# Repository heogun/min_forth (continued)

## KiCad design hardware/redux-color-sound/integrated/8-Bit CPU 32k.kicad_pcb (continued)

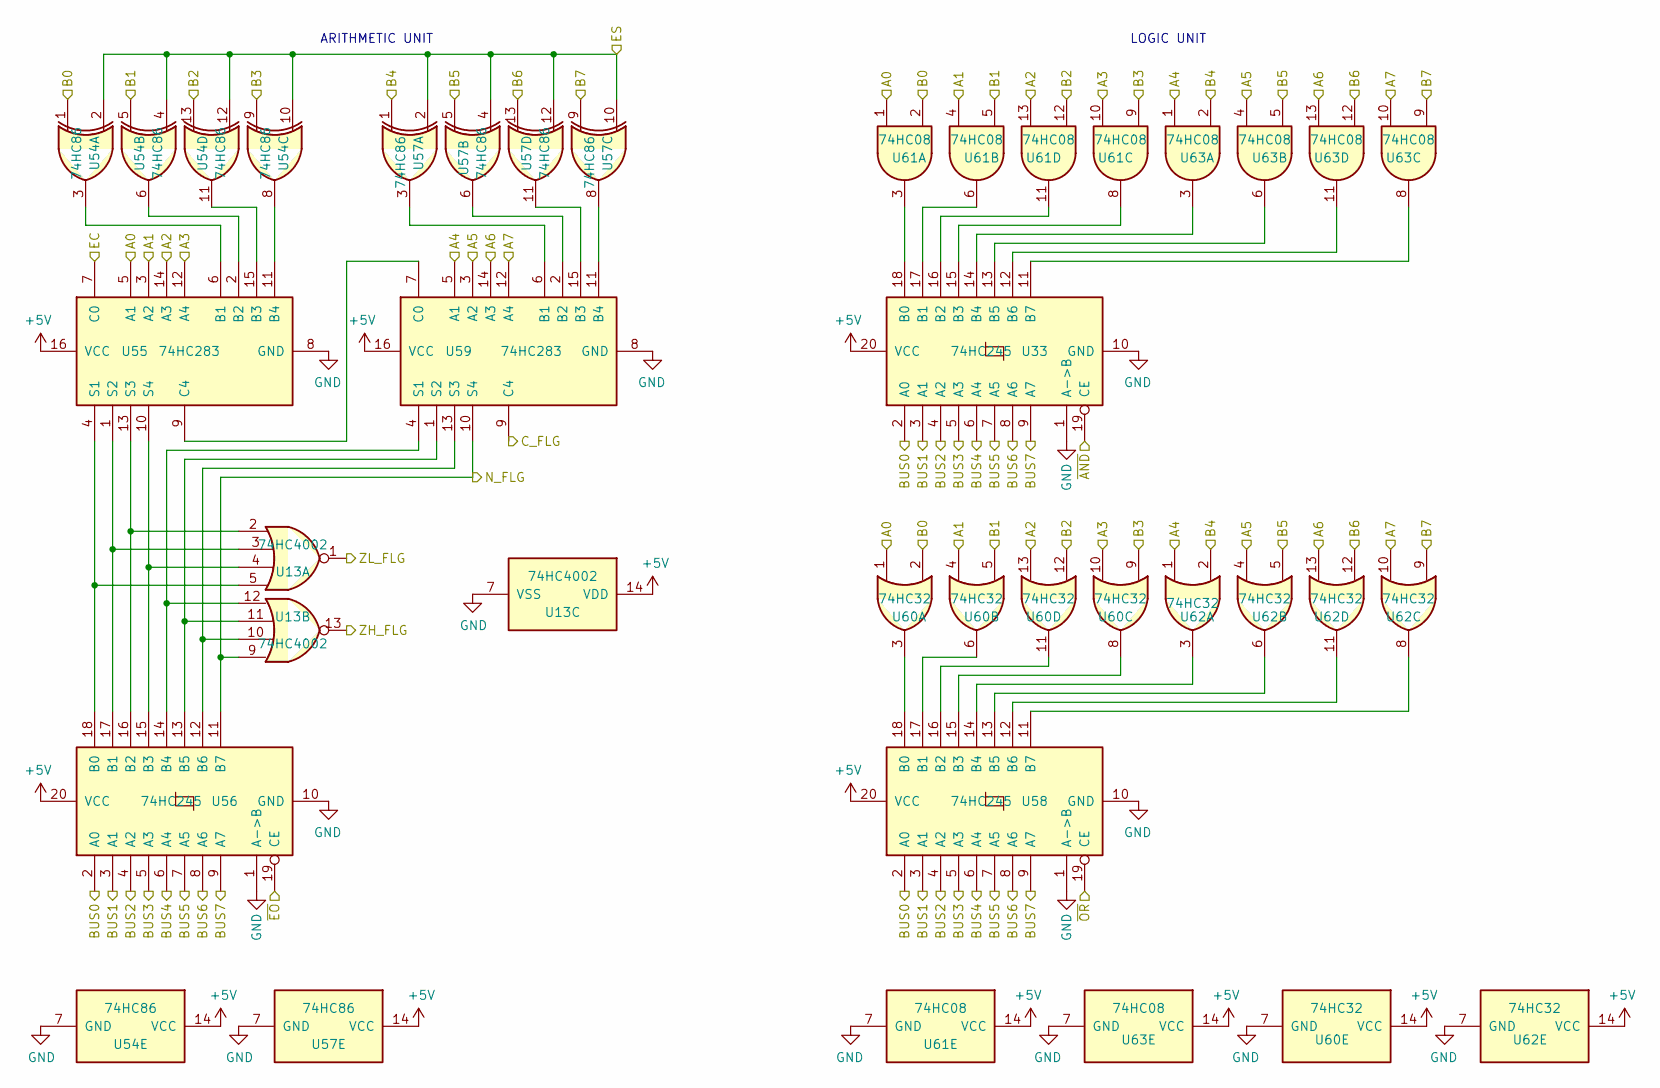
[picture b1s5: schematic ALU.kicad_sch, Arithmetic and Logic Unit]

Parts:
U13: 74HC4002; DIP-14_W7.62mm_Socket
U33, U56, U58: 74HC245; DIP-20_W7.62mm_Socket
U54, U57: 74HC86; DIP-14_W7.62mm_Socket
U55, U59: 74HC283; DIP-16_W7.62mm_Socket
U60, U62: 74HC32; DIP-14_W7.62mm_Socket
U61, U63: 74HC08; DIP-14_W7.62mm_Socket

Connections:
+5V: U13.14 (VDD), U33.20 (VCC), U54.14 (VCC), U55.16 (VCC), U56.20 (VCC), U57.14 (VCC), U58.20 (VCC), U59.16 (VCC), U60.14 (VCC), U61.14 (VCC), U62.14 (VCC), U63.14 (VCC); also elsewhere on the board
/ALU/A0: U55.5 (A1), U60.1, U61.1; also elsewhere on the board
/ALU/A1: U55.3 (A2), U60.4, U61.4; also elsewhere on the board
/ALU/A2: U55.14 (A3), U60.13, U61.13; also elsewhere on the board
/ALU/A3: U55.12 (A4), U60.10, U61.10; also elsewhere on the board
/ALU/A4: U59.5 (A1), U62.1, U63.1; also elsewhere on the board
/ALU/A5: U59.3 (A2), U62.4, U63.4; also elsewhere on the board
/ALU/A6: U59.14 (A3), U62.13, U63.13; also elsewhere on the board
/ALU/A7: U59.12 (A4), U62.10, U63.10; also elsewhere on the board
/ALU/B0: U54.1, U60.2, U61.2; also elsewhere on the board
/ALU/B1: U54.5, U60.5, U61.5; also elsewhere on the board
/ALU/B2: U54.13, U60.12, U61.12; also elsewhere on the board
/ALU/B3: U54.9, U60.9, U61.9; also elsewhere on the board
/ALU/B4: U57.1, U62.2, U63.2; also elsewhere on the board
/ALU/B5: U57.5, U62.5, U63.5; also elsewhere on the board
/ALU/B6: U57.13, U62.12, U63.12; also elsewhere on the board
/ALU/B7: U57.9, U62.9, U63.9; also elsewhere on the board
/ALU/C_FLG: U59.9 (C4); also elsewhere on the board
/ALU/EC: U55.7 (C0); also elsewhere on the board
/ALU/ES: U54.2, U54.4, U54.10, U54.12, U57.2, U57.4, U57.10, U57.12; also elsewhere on the board
/ALU/N_FLG: U13.9, U56.11 (B7), U59.10 (S4); also elsewhere on the board
/ALU/ZH_FLG: U13.13; also elsewhere on the board
/ALU/ZL_FLG: U13.1; also elsewhere on the board
/ALU/~AND: U33.19 (CE); also elsewhere on the board
/ALU/~EO: U56.19 (CE); also elsewhere on the board
/ALU/~OR: U58.19 (CE); also elsewhere on the board
BUS0: U33.2 (A0), U56.2 (A0), U58.2 (A0); also elsewhere on the board
BUS1: U33.3 (A1), U56.3 (A1), U58.3 (A1); also elsewhere on the board
BUS2: U33.4 (A2), U56.4 (A2), U58.4 (A2); also elsewhere on the board
BUS3: U33.5 (A3), U56.5 (A3), U58.5 (A3); also elsewhere on the board
BUS4: U33.6 (A4), U56.6 (A4), U58.6 (A4); also elsewhere on the board
BUS5: U33.7 (A5), U56.7 (A5), U58.7 (A5); also elsewhere on the board
BUS6: U33.8 (A6), U56.8 (A6), U58.8 (A6); also elsewhere on the board
BUS7: U33.9 (A7), U56.9 (A7), U58.9 (A7); also elsewhere on the board
GND: U13.7 (VSS), U33.1 (A->B), U33.10 (GND), U54.7 (GND), U55.8 (GND), U56.1 (A->B), U56.10 (GND), U57.7 (GND), U58.1 (A->B), U58.10 (GND), U59.8 (GND), U60.7 (GND), U61.7 (GND), U62.7 (GND), U63.7 (GND); also elsewhere on the board
unnamed: U33.18 (B0), U61.3
unnamed: U33.17 (B1), U61.6
unnamed: U33.16 (B2), U61.11
unnamed: U33.15 (B3), U61.8
unnamed: U33.14 (B4), U63.3
unnamed: U33.13 (B5), U63.6
unnamed: U33.12 (B6), U63.11
unnamed: U33.11 (B7), U63.8
unnamed: U54.3, U55.6 (B1)
unnamed: U54.6, U55.2 (B2)
unnamed: U54.11, U55.15 (B3)
unnamed: U54.8, U55.11 (B4)
unnamed: U55.9 (C4), U59.7 (C0)
unnamed: U13.5, U55.4 (S1), U56.18 (B0)
unnamed: U13.3, U55.1 (S2), U56.17 (B1)
unnamed: U13.2, U55.13 (S3), U56.16 (B2)
unnamed: U13.4, U55.10 (S4), U56.15 (B3)
unnamed: U13.12, U56.14 (B4), U59.4 (S1)
unnamed: U13.11, U56.13 (B5), U59.1 (S2)
unnamed: U13.10, U56.12 (B6), U59.13 (S3)
unnamed: U58.18 (B0), U60.3
unnamed: U58.17 (B1), U60.6
unnamed: U58.16 (B2), U60.11
unnamed: U58.15 (B3), U60.8
unnamed: U58.14 (B4), U62.3
unnamed: U58.13 (B5), U62.6
unnamed: U58.12 (B6), U62.11
unnamed: U58.11 (B7), U62.8
unnamed: U57.3, U59.6 (B1)
unnamed: U57.6, U59.2 (B2)
unnamed: U57.11, U59.15 (B3)
unnamed: U57.8, U59.11 (B4)

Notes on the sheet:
ARITHMETIC UNIT
LOGIC UNIT

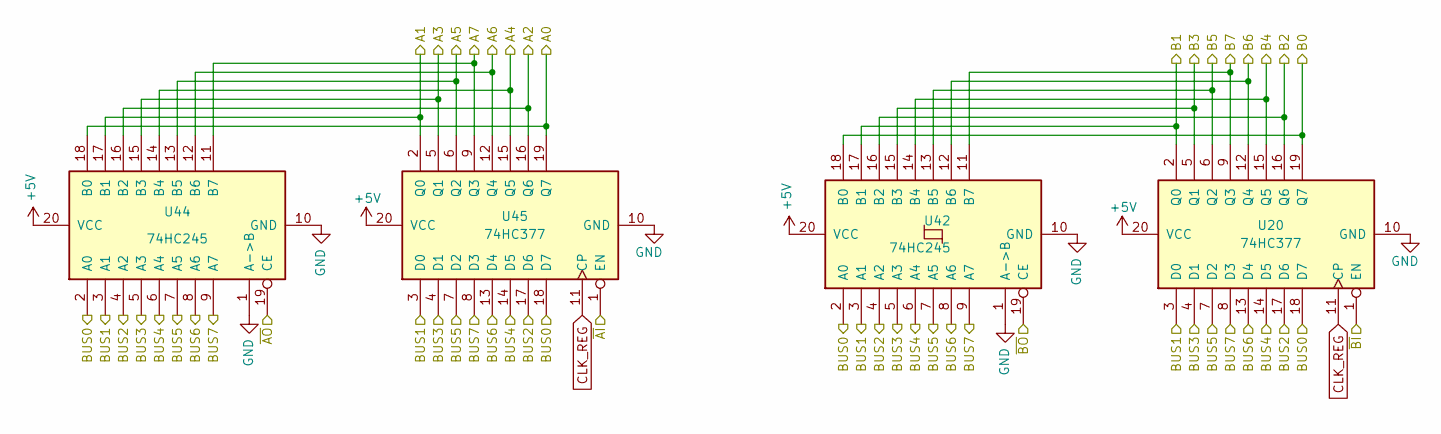
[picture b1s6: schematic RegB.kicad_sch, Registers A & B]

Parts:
U20, U45: 74HC377; DIP-20_W7.62mm_Socket
U42, U44: 74HC245; DIP-20_W7.62mm_Socket

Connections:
+5V: U20.20 (VCC), U42.20 (VCC), U44.20 (VCC), U45.20 (VCC); also elsewhere on the board
/ALU/A0: U44.18 (B0), U45.19 (Q7); also elsewhere on the board
/ALU/A1: U44.17 (B1), U45.2 (Q0); also elsewhere on the board
/ALU/A2: U44.16 (B2), U45.16 (Q6); also elsewhere on the board
/ALU/A3: U44.15 (B3), U45.5 (Q1); also elsewhere on the board
/ALU/A4: U44.14 (B4), U45.15 (Q5); also elsewhere on the board
/ALU/A5: U44.13 (B5), U45.6 (Q2); also elsewhere on the board
/ALU/A6: U44.12 (B6), U45.12 (Q4); also elsewhere on the board
/ALU/A7: U44.11 (B7), U45.9 (Q3); also elsewhere on the board
/ALU/B0: U20.19 (Q7), U42.18 (B0); also elsewhere on the board
/ALU/B1: U20.2 (Q0), U42.17 (B1); also elsewhere on the board
/ALU/B2: U20.16 (Q6), U42.16 (B2); also elsewhere on the board
/ALU/B3: U20.5 (Q1), U42.15 (B3); also elsewhere on the board
/ALU/B4: U20.15 (Q5), U42.14 (B4); also elsewhere on the board
/ALU/B5: U20.6 (Q2), U42.13 (B5); also elsewhere on the board
/ALU/B6: U20.12 (Q4), U42.12 (B6); also elsewhere on the board
/ALU/B7: U20.9 (Q3), U42.11 (B7); also elsewhere on the board
/Control Logic/~AI: U45.1 (EN); also elsewhere on the board
/Control Logic/~AO: U44.19 (CE); also elsewhere on the board
/Control Logic/~BI: U20.1 (EN); also elsewhere on the board
/Control Logic/~BO: U42.19 (CE); also elsewhere on the board
BUS0: U20.18 (D7), U42.2 (A0), U44.2 (A0), U45.18 (D7); also elsewhere on the board
BUS1: U20.3 (D0), U42.3 (A1), U44.3 (A1), U45.3 (D0); also elsewhere on the board
BUS2: U20.17 (D6), U42.4 (A2), U44.4 (A2), U45.17 (D6); also elsewhere on the board
BUS3: U20.4 (D1), U42.5 (A3), U44.5 (A3), U45.4 (D1); also elsewhere on the board
BUS4: U20.14 (D5), U42.6 (A4), U44.6 (A4), U45.14 (D5); also elsewhere on the board
BUS5: U20.7 (D2), U42.7 (A5), U44.7 (A5), U45.7 (D2); also elsewhere on the board
BUS6: U20.13 (D4), U42.8 (A6), U44.8 (A6), U45.13 (D4); also elsewhere on the board
BUS7: U20.8 (D3), U42.9 (A7), U44.9 (A7), U45.8 (D3); also elsewhere on the board
CLK_REG: U20.11 (CP), U45.11 (CP); also elsewhere on the board
GND: U20.10 (GND), U42.1 (A->B), U42.10 (GND), U44.1 (A->B), U44.10 (GND), U45.10 (GND); also elsewhere on the board

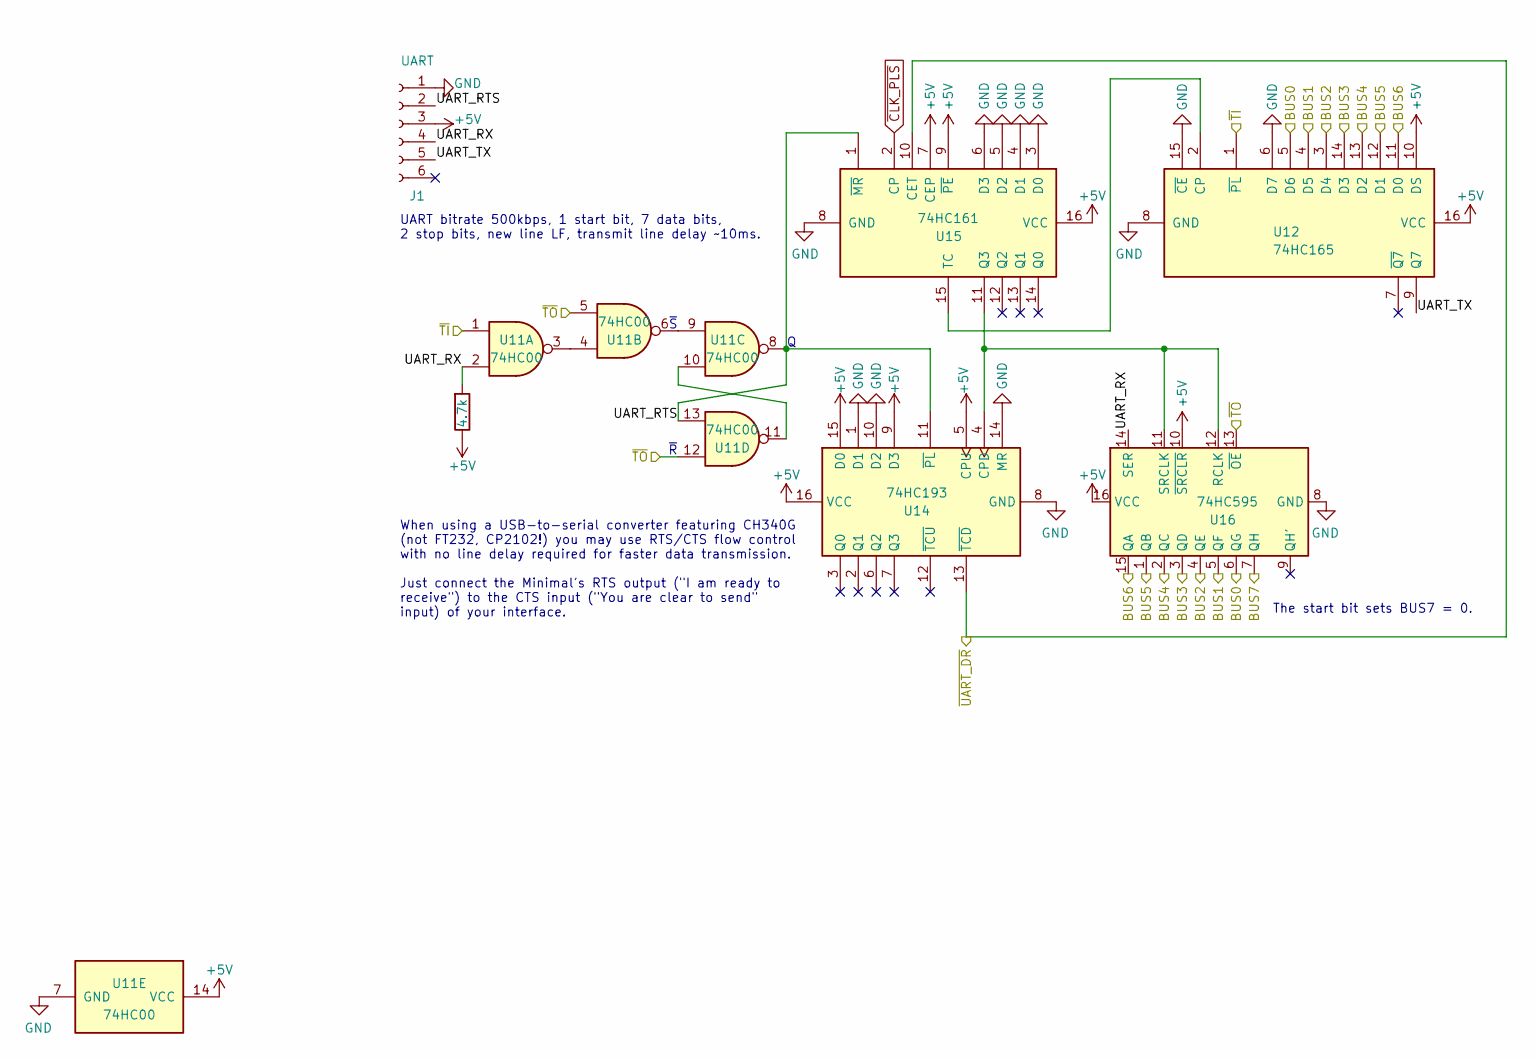
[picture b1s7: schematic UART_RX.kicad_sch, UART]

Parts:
J1: UART; PinSocket_1x06_P2.54mm_Vertical
R1: 4.7k; R_Axial_DIN0207_L6.3mm_D2.5mm_P7.62mm_Horizontal
U11: 74HC00; DIP-14_W7.62mm_Socket
U12: 74HC165; DIP-16_W7.62mm_Socket
U14: 74HC193; DIP-16_W7.62mm_Socket
U15: 74HC161; DIP-16_W7.62mm_Socket
U16: 74HC595; DIP-16_W7.62mm_Socket

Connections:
+5V: J1.3, R1.1, U11.14 (VCC), U12.10 (DS), U12.16 (VCC), U14.5 (CPU), U14.9 (D3), U14.15 (D0), U14.16 (VCC), U15.7 (CEP), U15.9 (~PE), U15.16 (VCC), U16.10 (~SRCLR), U16.16 (VCC); also elsewhere on the board
/Control Logic/~TI: U11.1, U12.1 (~PL); also elsewhere on the board
/Control Logic/~TO: U11.5, U11.12, U16.13 (~OE); also elsewhere on the board
/Control Logic/~UART_DR: U14.13 (~TCD), U15.10 (CET); also elsewhere on the board
/UART/UART_RTS: J1.2, U11.8, U11.13, U14.11 (~PL), U15.1 (~MR)
/UART/UART_RX: J1.4, R1.2, U11.2, U16.14 (SER)
/UART/UART_TX: J1.5, U12.9 (Q7)
BUS0: U12.5 (D6), U16.6 (QG); also elsewhere on the board
BUS1: U12.4 (D5), U16.5 (QF); also elsewhere on the board
BUS2: U12.3 (D4), U16.4 (QE); also elsewhere on the board
BUS3: U12.14 (D3), U16.3 (QD); also elsewhere on the board
BUS4: U12.13 (D2), U16.2 (QC); also elsewhere on the board
BUS5: U12.12 (D1), U16.1 (QB); also elsewhere on the board
BUS6: U12.11 (D0), U16.15 (QA); also elsewhere on the board
BUS7: U16.7 (QH); also elsewhere on the board
GND: J1.1, U11.7 (GND), U12.6 (D7), U12.8 (GND), U12.15 (~CE), U14.1 (D1), U14.8 (GND), U14.10 (D2), U14.14 (MR), U15.3 (D0), U15.4 (D1), U15.5 (D2), U15.6 (D3), U15.8 (GND), U16.8 (GND); also elsewhere on the board
unnamed: U11.3, U11.4
unnamed: U11.6, U11.9
unnamed: U11.10, U11.11
unnamed: U12.2 (CP), U15.15 (TC)
unnamed: U14.4 (CPD), U15.11 (Q3), U16.11 (SRCLK), U16.12 (RCLK)
~CLK_PLS: U15.2 (CP); also elsewhere on the board

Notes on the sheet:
~{S}
UART bitrate 500kbps, 1 start bit, 7 data bits, 2 stop bits, new line LF, transmit line delay ~10ms.
~{R}
The start bit sets BUS7 = 0.
When using a USB-to-serial converter featuring CH340G (not FT232, CP2102!) you may use RTS/CTS flow control with no line delay required for faster data transmission. Just connect the Minimal's RTS output ("I am ready to receive") to the CTS input ("You are clear to send" input) of your interface.

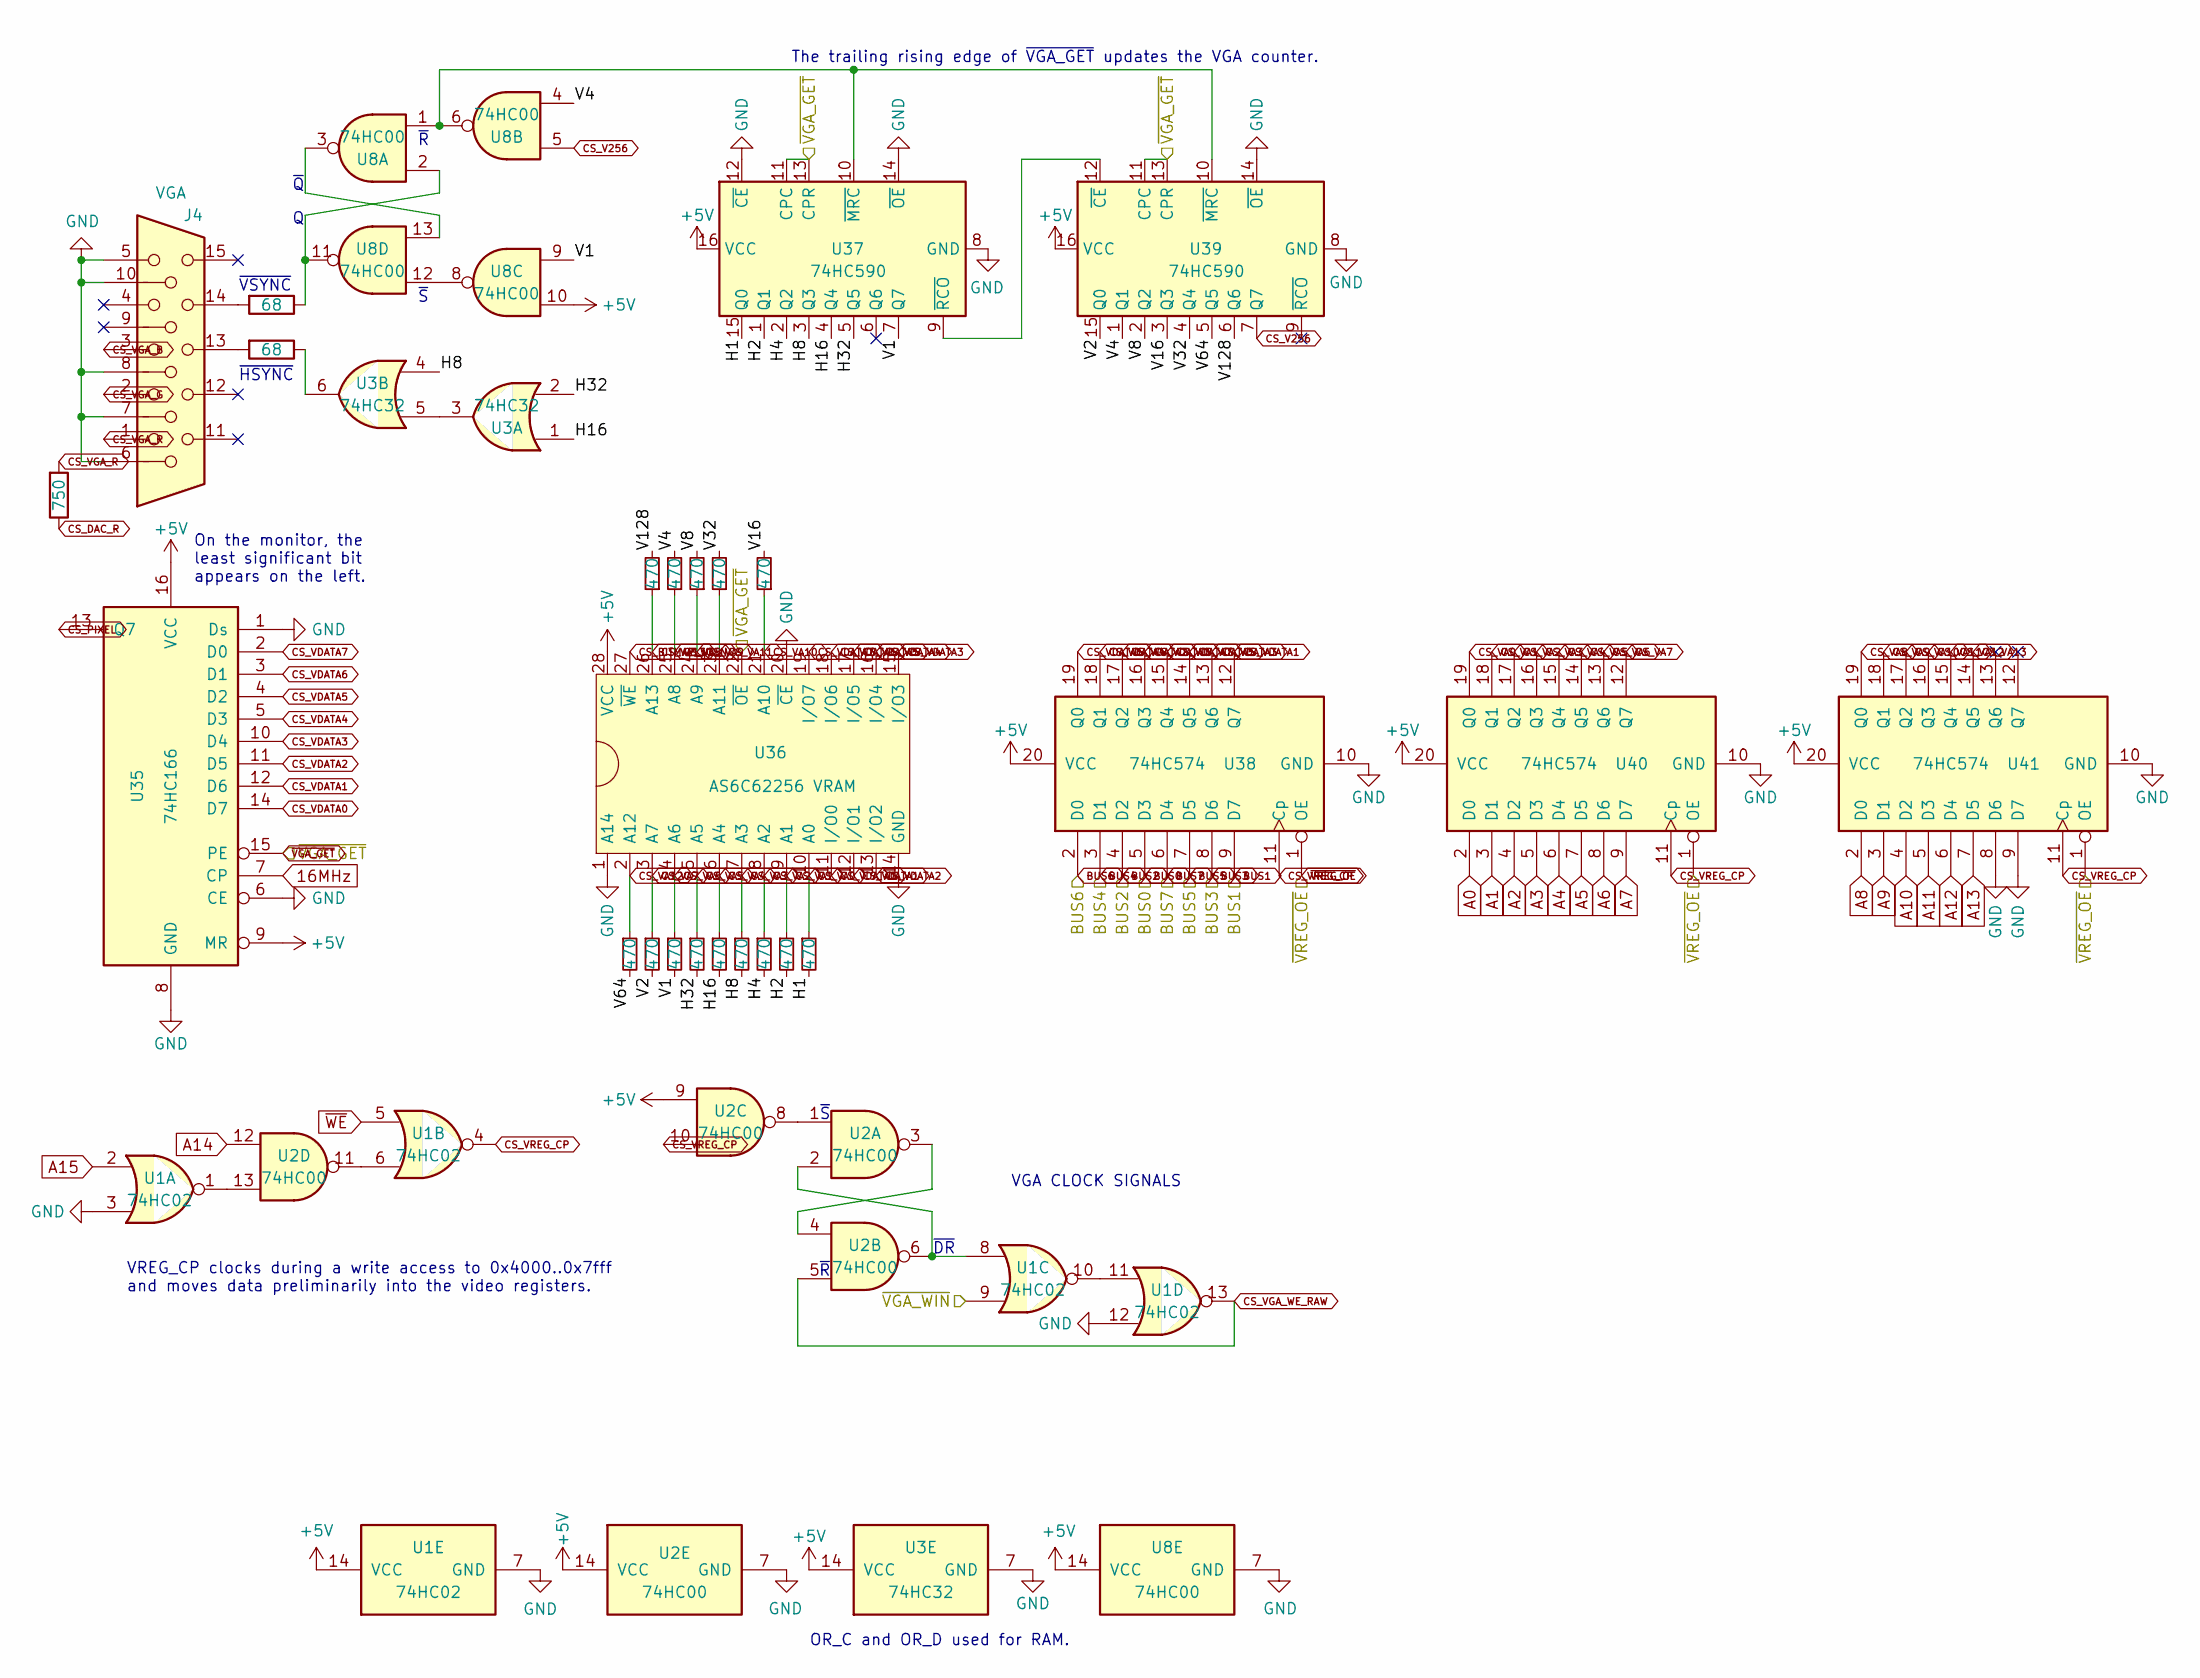
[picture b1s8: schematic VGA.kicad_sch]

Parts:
J4: VGA; VGA DSUB15HD_female
R6: 750; R_Axial_DIN0207_L6.3mm_D2.5mm_P7.62mm_Horizontal
R7, R8: 68; R_Axial_DIN0207_L6.3mm_D2.5mm_P7.62mm_Horizontal
R9, R10, R11, R12, R13, R14, R15, R16, R17, R18, R19, R20, R21, R22: 470; R_Axial_DIN0207_L6.3mm_D2.5mm_P7.62mm_Horizontal
U1: 74HC02; DIP-14_W7.62mm_Socket
U2, U8: 74HC00; DIP-14_W7.62mm_Socket
U3: 74HC32; DIP-14_W7.62mm_Socket
U35: 74HC166; DIP-16_W7.62mm_Socket
U36: AS6C62256 VRAM; DIP-28_W15.24mm_Socket
U37, U39: 74HC590; DIP-16_W7.62mm_Socket
U38, U40, U41: 74HC574; DIP-20_W7.62mm_Socket

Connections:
16MHz: U35.7 (CP); also elsewhere on the board
+5V: U1.14 (VCC), U2.9, U2.14 (VCC), U3.14 (VCC), U8.10, U8.14 (VCC), U35.9 (MR), U35.16 (VCC), U36.28 (VCC), U37.16 (VCC), U38.20 (VCC), U39.16 (VCC), U40.20 (VCC), U41.20 (VCC); also elsewhere on the board
/Control Logic/~VGA_WIN: U1.9; also elsewhere on the board
/VGA/H1: R9.2, U37.15 (Q0)
/VGA/H2: R10.2, U37.1 (Q1)
/VGA/H4: R11.2, U37.2 (Q2)
/VGA/H8: R12.2, U3.4, U37.3 (Q3)
/VGA/H16: R13.2, U3.1, U37.4 (Q4)
/VGA/H32: R14.2, U3.2, U37.5 (Q5)
/VGA/V1: R15.2, U8.9, U37.7 (Q7)
/VGA/V2: R16.2, U39.15 (Q0)
/VGA/V4: R17.2, U8.4, U39.1 (Q1)
/VGA/V8: R18.2, U39.2 (Q2)
/VGA/V16: R19.2, U39.3 (Q3)
/VGA/V32: R20.2, U39.4 (Q4)
/VGA/V64: R21.2, U39.5 (Q5)
/VGA/V128: R22.2, U39.6 (Q6)
A0: U40.2 (D0); also elsewhere on the board
A1: U40.3 (D1); also elsewhere on the board
A2: U40.4 (D2); also elsewhere on the board
A3: U40.5 (D3); also elsewhere on the board
A4: U40.6 (D4); also elsewhere on the board
A5: U40.7 (D5); also elsewhere on the board
A6: U40.8 (D6); also elsewhere on the board
A7: U40.9 (D7); also elsewhere on the board
A8: U41.2 (D0); also elsewhere on the board
A9: U41.3 (D1); also elsewhere on the board
A10: U41.4 (D2); also elsewhere on the board
A11: U41.5 (D3); also elsewhere on the board
A12: U41.6 (D4); also elsewhere on the board
A13: U41.7 (D5); also elsewhere on the board
A14: U2.12; also elsewhere on the board
A15: U1.2; also elsewhere on the board
BUS0: U38.5 (D3); also elsewhere on the board
BUS1: U38.9 (D7); also elsewhere on the board
BUS2: U38.4 (D2); also elsewhere on the board
BUS3: U38.8 (D6); also elsewhere on the board
BUS4: U38.3 (D1); also elsewhere on the board
BUS5: U38.7 (D5); also elsewhere on the board
BUS6: U38.2 (D0); also elsewhere on the board
BUS7: U38.6 (D4); also elsewhere on the board
CS_BITMAP_WE_N: U36.27 (~WE); also elsewhere on the board
CS_DAC_R: R6.1; also elsewhere on the board
CS_PIXEL: U35.13 (Q7); also elsewhere on the board
CS_V256: U8.5, U39.7 (Q7); also elsewhere on the board
CS_VA0: R9.1, U36.10 (A0), U40.19 (Q0); also elsewhere on the board
CS_VA1: R10.1, U36.9 (A1), U40.18 (Q1); also elsewhere on the board
CS_VA2: R11.1, U36.8 (A2), U40.17 (Q2); also elsewhere on the board
CS_VA3: R12.1, U36.7 (A3), U40.16 (Q3); also elsewhere on the board
CS_VA4: R13.1, U36.6 (A4), U40.15 (Q4); also elsewhere on the board
CS_VA5: R14.1, U36.5 (A5), U40.14 (Q5); also elsewhere on the board
CS_VA6: R15.1, U36.4 (A6), U40.13 (Q6)
CS_VA7: R16.1, U36.3 (A7), U40.12 (Q7)
CS_VA8: R17.1, U36.25 (A8), U41.19 (Q0); also elsewhere on the board
CS_VA9: R18.1, U36.24 (A9), U41.18 (Q1); also elsewhere on the board
CS_VA10: R19.1, U36.21 (A10), U41.17 (Q2); also elsewhere on the board
CS_VA11: R20.1, U36.23 (A11), U41.16 (Q3); also elsewhere on the board
CS_VA12: R21.1, U36.2 (A12), U41.15 (Q4); also elsewhere on the board
CS_VA13: R22.1, U36.26 (A13), U41.14 (Q5); also elsewhere on the board
CS_VDATA0: U35.14 (D7), U36.11 (I/O0), U38.16 (Q3); also elsewhere on the board
CS_VDATA1: U35.12 (D6), U36.12 (I/O1), U38.12 (Q7); also elsewhere on the board
CS_VDATA2: U35.11 (D5), U36.13 (I/O2), U38.17 (Q2); also elsewhere on the board
CS_VDATA3: U35.10 (D4), U36.15 (I/O3), U38.13 (Q6); also elsewhere on the board
CS_VDATA4: U35.5 (D3), U36.16 (I/O4), U38.18 (Q1); also elsewhere on the board
CS_VDATA5: U35.4 (D2), U36.17 (I/O5), U38.14 (Q5); also elsewhere on the board
CS_VDATA6: U35.3 (D1), U36.18 (I/O6), U38.19 (Q0); also elsewhere on the board
CS_VDATA7: U35.2 (D0), U36.19 (I/O7), U38.15 (Q4); also elsewhere on the board
CS_VGA_B: J4.3; also elsewhere on the board
CS_VGA_G: J4.2; also elsewhere on the board
CS_VGA_R: J4.1, R6.2; also elsewhere on the board
CS_VGA_WE_RAW: U1.13, U2.5; also elsewhere on the board
CS_VREG_CP: U1.4, U2.10, U38.11 (Cp), U40.11 (Cp), U41.11 (Cp); also elsewhere on the board
GND: J4.5, J4.6, J4.7, J4.8, J4.10, U1.3, U1.7 (GND), U1.12, U2.7 (GND), U3.7 (GND), U8.7 (GND), U35.1 (Ds), U35.6 (CE), U35.8 (GND), U36.1 (A14), U36.14 (GND), U36.20 (~CE), U37.8 (GND), U37.12 (~CE), U37.14 (~OE), U38.10 (GND), U39.8 (GND), U39.14 (~OE), U40.10 (GND), U41.8 (D6), U41.9 (D7), U41.10 (GND); also elsewhere on the board
unnamed: J4.13, R8.2
unnamed: J4.14, R7.2
unnamed: R7.1, U8.2, U8.11
unnamed: R8.1, U3.6
unnamed: U1.1, U2.13
unnamed: U1.6, U2.11
unnamed: U1.8, U2.2, U2.6
unnamed: U1.10, U1.11
unnamed: U2.1, U2.8
unnamed: U2.3, U2.4
unnamed: U3.3, U3.5
unnamed: U8.8, U8.12
unnamed: U8.3, U8.13
unnamed: U8.1, U8.6, U37.10 (~MRC), U39.10 (~MRC)
unnamed: U37.9 (~RCO), U39.12 (~CE)
~VGA_GET: U35.15 (PE), U36.22 (~OE), U37.11 (CPC), U37.13 (CPR), U39.11 (CPC), U39.13 (CPR); also elsewhere on the board
~VREG_OE: U38.1 (OE), U40.1 (OE), U41.1 (OE); also elsewhere on the board
~WE: U1.5; also elsewhere on the board

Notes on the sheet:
~{S}
VREG_CP clocks during a write access to 0x4000..0x7fff and moves data preliminarily into the video registers.
~{DR}
~{R}
On the monitor, the least significant bit appears on the left.
~{Q}
~{HSYNC}
OR_C and OR_D used for RAM.
~{VSYNC}
The trailing rising edge of ~{VGA_GET} updates the VGA counter.
VGA CLOCK SIGNALS

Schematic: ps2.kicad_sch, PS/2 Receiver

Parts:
J2: PS/2; FP_MINI_DIN_6_PS2
R3, R4: 4.7k; R_Axial_DIN0207_L6.3mm_D2.5mm_P7.62mm_Horizontal
U9: 74HCT132; DIP-14_W7.62mm_Socket
U17: 74HC595; DIP-16_W7.62mm_Socket
U18: 74HC193; DIP-16_W7.62mm_Socket

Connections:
+5V: J2.4, R3.1, R4.1, U9.9, U9.14 (VCC), U17.10 (~SRCLR), U17.16 (VCC), U18.1 (D1), U18.5 (CPU), U18.9 (D3), U18.16 (VCC); also elsewhere on the board
/Control Logic/~KO: U9.5, U17.13 (~OE); also elsewhere on the board
/Control Logic/~PS2_DR: U9.12, U18.13 (~TCD); also elsewhere on the board
/PS2 Receiver/PS2_CLK: J2.5, R3.2, U9.13
/PS2 Receiver/PS2_DAT: J2.1, R4.2, U9.1, U17.14 (SER)
BUS0: U17.7 (QH); also elsewhere on the board
BUS1: U17.6 (QG); also elsewhere on the board
BUS2: U17.5 (QF); also elsewhere on the board
BUS3: U17.4 (QE); also elsewhere on the board
BUS4: U17.3 (QD); also elsewhere on the board
BUS5: U17.2 (QC); also elsewhere on the board
BUS6: U17.1 (QB); also elsewhere on the board
BUS7: U17.15 (QA); also elsewhere on the board
GND: J2.3, U9.7 (GND), U17.8 (GND), U18.8 (GND), U18.10 (D2), U18.14 (MR), U18.15 (D0); also elsewhere on the board
unnamed: U9.2, U9.6
unnamed: U9.10, U9.11
unnamed: U17.12 (RCLK), U18.3 (Q0)
unnamed: U9.8, U17.11 (SRCLK), U18.4 (CPD)
unnamed: U9.3, U9.4, U18.11 (~PL)

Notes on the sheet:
(green)
(yellow)
~{Q}
The order of the bits is intentionally reversed.
~{TCD} goes LOW at the falling edge of CPD after reaching zero at the beginning of the high stop bit ensuring that a full transmission has been sampled. Note that RCLK is driven by Q0 which happens *after* CPD. Thus RCLK always samples the *current*, not the previous register state. RCLK is driven 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
For PS/2 devices with only 3.3V output use 74HCT132 for maximum robustness.
~{R}
~{S}
74HCxx input rise time (10-90%) is required to be <400ns. Use 74HC132 (NAND with Schmitt trigger inputs) rather than 74HC00 here, since PS/2 signals can have rise and fall times >400ns.

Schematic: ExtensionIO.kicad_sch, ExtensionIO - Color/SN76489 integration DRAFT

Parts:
U64: 74HC30; DIP-14_W7.62mm_Socket
U65: 74HC04; DIP-14_W7.62mm_Socket
U66: 74HC138; DIP-16_W7.62mm_Socket
U67, U68: 74HC11; DIP-14_W7.62mm_Socket
U69: 74HC173; DIP-16_W7.62mm_Socket
U70: 74HC377; DIP-20_W7.62mm_Socket
U71, U72: 74HC32; DIP-14_W7.62mm_Socket

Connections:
+5V: U64.14 (VCC), U65.14 (VCC), U66.16 (VCC), U67.14 (VCC), U68.14 (VCC), U69.16 (VCC), U70.20 (VCC), U71.14 (VCC), U72.14 (VCC); also elsewhere on the board
A0: U66.1 (A0); also elsewhere on the board
A1: U66.2 (A1); also elsewhere on the board
A2: U66.3 (A2); also elsewhere on the board
A4: U65.5, U66.5 (~E1); also elsewhere on the board
A5: U67.13; also elsewhere on the board
A6: U67.2; also elsewhere on the board
A7: U67.1; also elsewhere on the board
A8: U65.1; also elsewhere on the board
A9: U64.11; also elsewhere on the board
A10: U64.6; also elsewhere on the board
A11: U64.5; also elsewhere on the board
A12: U64.4; also elsewhere on the board
A13: U64.3; also elsewhere on the board
A14: U64.2, U68.2; also elsewhere on the board
A15: U64.1; also elsewhere on the board
BUS0: U69.14 (D0), U70.3 (D0); also elsewhere on the board
BUS1: U69.13 (D1), U70.4 (D1); also elsewhere on the board
BUS2: U69.12 (D2), U70.7 (D2); also elsewhere on the board
BUS3: U69.11 (D3), U70.8 (D3); also elsewhere on the board
BUS4: U70.13 (D4); also elsewhere on the board
BUS5: U70.14 (D5); also elsewhere on the board
BUS6: U70.17 (D6); also elsewhere on the board
BUS7: U70.18 (D7); also elsewhere on the board
CLK_MAR: U69.7 (Cp), U70.11 (CP); also elsewhere on the board
CS_A4_N: U65.6, U67.5
CS_A8_N: U64.12, U65.2
CS_A15_N: U68.13; also elsewhere on the board
CS_ATTR_CPU: U68.12, U71.5
CS_ATTR_MODE: U68.1, U69.5 (Q2); also elsewhere on the board
CS_ATTR_WE_N: U71.11; also elsewhere on the board
CS_AUDIO_EN: U65.11, U69.6 (Q3); also elsewhere on the board
CS_AUDIO_MUTE: U65.10; also elsewhere on the board
CS_BITMAP_WE_N: U71.8; also elsewhere on the board
CS_COLOR_EN: U69.3 (Q0); also elsewhere on the board
CS_FE: U65.4, U67.3
CS_FE_N: U64.8, U65.3, U66.4 (~E0)
CS_INH_EXT: U71.1; also elsewhere on the board
CS_INH_IO: U71.3, U71.4
CS_IO_HIT: U67.6, U71.2
CS_LO: U66.6 (E2), U67.4, U67.12
CS_PENDING_ATTR: U71.10; also elsewhere on the board
CS_PENDING_BITMAP: U71.13; also elsewhere on the board
CS_RAM_INH: U71.6; also elsewhere on the board
CS_RESET: U65.12, U69.15 (Mr); also elsewhere on the board
CS_SND0: U70.2 (Q0); also elsewhere on the board
CS_SND1: U70.5 (Q1); also elsewhere on the board
CS_SND2: U70.6 (Q2); also elsewhere on the board
CS_SND3: U70.9 (Q3); also elsewhere on the board
CS_SND4: U70.12 (Q4); also elsewhere on the board
CS_SND5: U70.15 (Q5); also elsewhere on the board
CS_SND6: U70.16 (Q6); also elsewhere on the board
CS_SND7: U70.19 (Q7); also elsewhere on the board
CS_SND_EN_N: U70.1 (~E), U72.6
CS_SN_WRITE: U65.9, U69.4 (Q1)
CS_SN_WRITE_N: U65.8; also elsewhere on the board
CS_STATUS_OE_N: U72.3; also elsewhere on the board
CS_VGA_WE_RAW: U71.9, U71.12; also elsewhere on the board
CS_Y0_N: U66.15 (~Y0), U72.4
CS_Y1_N: U66.14 (~Y1), U72.1
CS_Y2_N: U66.13 (~Y2), U69.9 (E1)
GND: U64.7 (GND), U65.7 (GND), U66.8 (GND), U67.7 (GND), U67.9, U67.10, U67.11, U68.3, U68.4, U68.5, U68.7 (GND), U68.9, U68.10, U68.11, U69.1 (Oe1), U69.2 (Oe2), U69.8 (GND), U70.10 (GND), U71.7 (GND), U72.7 (GND), U72.9, U72.10, U72.12, U72.13; also elsewhere on the board
~RESET: U65.13; also elsewhere on the board
~RI: U69.10 (E2), U72.5; also elsewhere on the board
~RO: U72.2; also elsewhere on the board

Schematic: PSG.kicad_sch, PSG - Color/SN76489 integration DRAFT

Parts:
C62: 220n; C_Disc_D5.0mm_W2.5mm_P2.50mm
J6: MONO LINE OUT / EXTERNAL AMP; PinHeader_1x02_P2.54mm_Vertical
Q1: 2N7000; TO-92_Inline
R33: 4.7k; R_Axial_DIN0207_L6.3mm_D2.5mm_P7.62mm_Horizontal
R34: 1k; R_Axial_DIN0207_L6.3mm_D2.5mm_P7.62mm_Horizontal
R35: 10k; R_Axial_DIN0207_L6.3mm_D2.5mm_P7.62mm_Horizontal
R36: 100k; R_Axial_DIN0207_L6.3mm_D2.5mm_P7.62mm_Horizontal
U74: SN76489AN; DIP-16_W7.62mm_Socket
U75: 74HCT244; DIP-20_W7.62mm_Socket
U76: MCP130-450DI/TO; TO-92_Inline
X2: 3.579545MHz 5V FULL; Oscillator_DIP-14

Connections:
+5V: R33.1, R36.1, U74.16 (V_{CC}), U75.20 (VCC), U76.2 (VDD), X2.14 (VCC); also elsewhere on the board
BUS0: U75.18 (1Y0); also elsewhere on the board
BUS1: U75.16 (1Y1); also elsewhere on the board
BUS2: U75.14 (1Y2); also elsewhere on the board
BUS3: U75.12 (1Y3); also elsewhere on the board
BUS4: U75.9 (2Y3); also elsewhere on the board
BUS5: U75.7 (2Y2); also elsewhere on the board
BUS6: U75.5 (2Y1); also elsewhere on the board
BUS7: U75.3 (2Y0); also elsewhere on the board
CS_ATTR_MODE: U75.4 (1A1); also elsewhere on the board
CS_AUDIO_AC: C62.2, R34.1
CS_AUDIO_EN: U75.8 (1A3); also elsewhere on the board
CS_AUDIO_MUTE: Q1.2 (G), R36.2; also elsewhere on the board
CS_AUDIO_RAW: C62.1, U74.7 (AUDIO_OUT)
CS_COLOR_EN: U75.6 (1A2); also elsewhere on the board
CS_LINE_OUT: J6.1, Q1.3 (D), R34.2, R35.1
CS_SND0: U74.10 (D7); also elsewhere on the board
CS_SND1: U74.11 (D6); also elsewhere on the board
CS_SND2: U74.12 (D5); also elsewhere on the board
CS_SND3: U74.13 (D4); also elsewhere on the board
CS_SND4: U74.15 (D3); also elsewhere on the board
CS_SND5: U74.1 (D2); also elsewhere on the board
CS_SND6: U74.2 (D1); also elsewhere on the board
CS_SND7: U74.3 (D0); also elsewhere on the board
CS_SN_CLK: U74.14 (CLOCK), X2.8 (OUT)
CS_SN_READY: R33.2, U74.4 (READY), U75.2 (1A0)
CS_SN_WRITE_N: U74.5 (~WE), U74.6 (~CE); also elsewhere on the board
CS_STATUS_OE_N: U75.1 (1OE), U75.19 (2OE); also elsewhere on the board
GND: J6.2, Q1.1 (S), R35.2, U74.8 (GND), U75.10 (GND), U75.11 (2A3), U75.13 (2A2), U75.15 (2A1), U75.17 (2A0), U76.3 (VSS), X2.7 (GND); also elsewhere on the board
~RESET: U76.1 (~RST); also elsewhere on the board

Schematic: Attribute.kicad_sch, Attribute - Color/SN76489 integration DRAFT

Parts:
U77: AS6C62256-55PCN ATTRIBUTE; DIP-28_W15.24mm_Socket
U78: 74HC283; DIP-16_W7.62mm_Socket
U79: 74HC86; DIP-14_W7.62mm_Socket
U80: 74HC245; DIP-20_W7.62mm_Socket
U81: 74HCT377; DIP-20_W7.62mm_Socket
U82: 74HC74; DIP-14_W7.62mm_Socket

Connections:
16MHz: U81.11 (CP); also elsewhere on the board
+5V: U77.28 (VCC), U78.16 (VCC), U79.5, U79.10, U79.14 (VCC), U80.1 (A->B), U80.20 (VCC), U81.20 (VCC), U82.4 (~S), U82.10 (~S), U82.14 (VCC); also elsewhere on the board
A15: U79.4; also elsewhere on the board
CS_A15_N: U79.6; also elsewhere on the board
CS_ACTIVE_LATCH: U79.9; also elsewhere on the board
CS_ATTR_D0: U77.11 (I/O0), U80.18 (B0), U81.3 (D0)
CS_ATTR_D1: U77.12 (I/O1), U80.17 (B1), U81.4 (D1)
CS_ATTR_D2: U77.13 (I/O2), U80.16 (B2), U81.7 (D2)
CS_ATTR_D3: U77.15 (I/O3), U80.15 (B3), U81.8 (D3)
CS_ATTR_D4: U77.16 (I/O4), U80.14 (B4), U81.13 (D4)
CS_ATTR_D5: U77.17 (I/O5), U80.13 (B5), U81.14 (D5)
CS_ATTR_D6: U77.18 (I/O6), U80.12 (B6), U81.17 (D6)
CS_ATTR_D7: U77.19 (I/O7), U80.11 (B7), U81.18 (D7)
CS_ATTR_MODE: U82.2 (D); also elsewhere on the board
CS_ATTR_Q0: U81.2 (Q0); also elsewhere on the board
CS_ATTR_Q1: U81.5 (Q1); also elsewhere on the board
CS_ATTR_Q2: U81.6 (Q2); also elsewhere on the board
CS_ATTR_Q3: U81.9 (Q3); also elsewhere on the board
CS_ATTR_Q4: U81.12 (Q4); also elsewhere on the board
CS_ATTR_Q5: U81.15 (Q5); also elsewhere on the board
CS_ATTR_Q6: U81.16 (Q6); also elsewhere on the board
CS_ATTR_Q7: U81.19 (Q7); also elsewhere on the board
CS_ATTR_WE_N: U77.27 (~WE); also elsewhere on the board
CS_CA6: U77.4 (A6), U78.4 (S1)
CS_CA7: U77.3 (A7), U78.1 (S2); also elsewhere on the board
CS_CA8: U77.25 (A8), U78.13 (S3); also elsewhere on the board
CS_CA9: U77.24 (A9), U78.10 (S4); also elsewhere on the board
CS_CA10: U77.21 (A10), U79.3; also elsewhere on the board
CS_PENDING_ATTR: U82.5 (Q); also elsewhere on the board
CS_PENDING_BITMAP: U82.6 (~Q); also elsewhere on the board
CS_RGB_BLANK: U79.8; also elsewhere on the board
CS_ROW_CARRY: U78.9 (C4), U79.1
CS_VA0: U77.10 (A0); also elsewhere on the board
CS_VA1: U77.9 (A1); also elsewhere on the board
CS_VA2: U77.8 (A2); also elsewhere on the board
CS_VA3: U77.7 (A3); also elsewhere on the board
CS_VA4: U77.6 (A4); also elsewhere on the board
CS_VA5: U77.5 (A5); also elsewhere on the board
CS_VA8: U78.7 (C0); also elsewhere on the board
CS_VA9: U78.5 (A1); also elsewhere on the board
CS_VA10: U78.3 (A2); also elsewhere on the board
CS_VA11: U78.14 (A3); also elsewhere on the board
CS_VA12: U78.12 (A4); also elsewhere on the board
CS_VA13: U79.2; also elsewhere on the board
CS_VDATA0: U80.2 (A0); also elsewhere on the board
CS_VDATA1: U80.3 (A1); also elsewhere on the board
CS_VDATA2: U80.4 (A2); also elsewhere on the board
CS_VDATA3: U80.5 (A3); also elsewhere on the board
CS_VDATA4: U80.6 (A4); also elsewhere on the board
CS_VDATA5: U80.7 (A5); also elsewhere on the board
CS_VDATA6: U80.8 (A6); also elsewhere on the board
CS_VDATA7: U80.9 (A7); also elsewhere on the board
CS_VREG_CP: U82.3 (C); also elsewhere on the board
GND: U77.1 (A14), U77.2 (A12), U77.14 (GND), U77.20 (~CE), U77.23 (A11), U77.26 (A13), U78.2 (B2), U78.6 (B1), U78.8 (GND), U78.11 (B4), U78.15 (B3), U79.7 (GND), U79.12, U79.13, U80.10 (GND), U81.10 (GND), U82.7 (GND), U82.11 (C), U82.12 (D); also elsewhere on the board
~RESET: U82.1 (~R), U82.13 (~R); also elsewhere on the board
~VGA_GET: U77.22 (~OE), U81.1 (~E); also elsewhere on the board
~VREG_OE: U80.19 (CE); also elsewhere on the board

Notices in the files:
hardware/redux-color-sound/cad/ALU.kicad_sch:
creativecommons.org/licenses/by-nc-sa/4.0
This work is licensed under CC BY-NC-SA 4.0
hardware/redux-color-sound/integrated/8-Bit CPU 32k.kicad_pcb:
Licensed under CC BY-NC-SA 4.0  http://creativecommons.org/licenses/by-nc-sa/4.0
hardware/redux-color-sound/integrated/Attribute.kicad_sch:
Derived from slu4 Redux; CC BY-NC-SA 4.0
